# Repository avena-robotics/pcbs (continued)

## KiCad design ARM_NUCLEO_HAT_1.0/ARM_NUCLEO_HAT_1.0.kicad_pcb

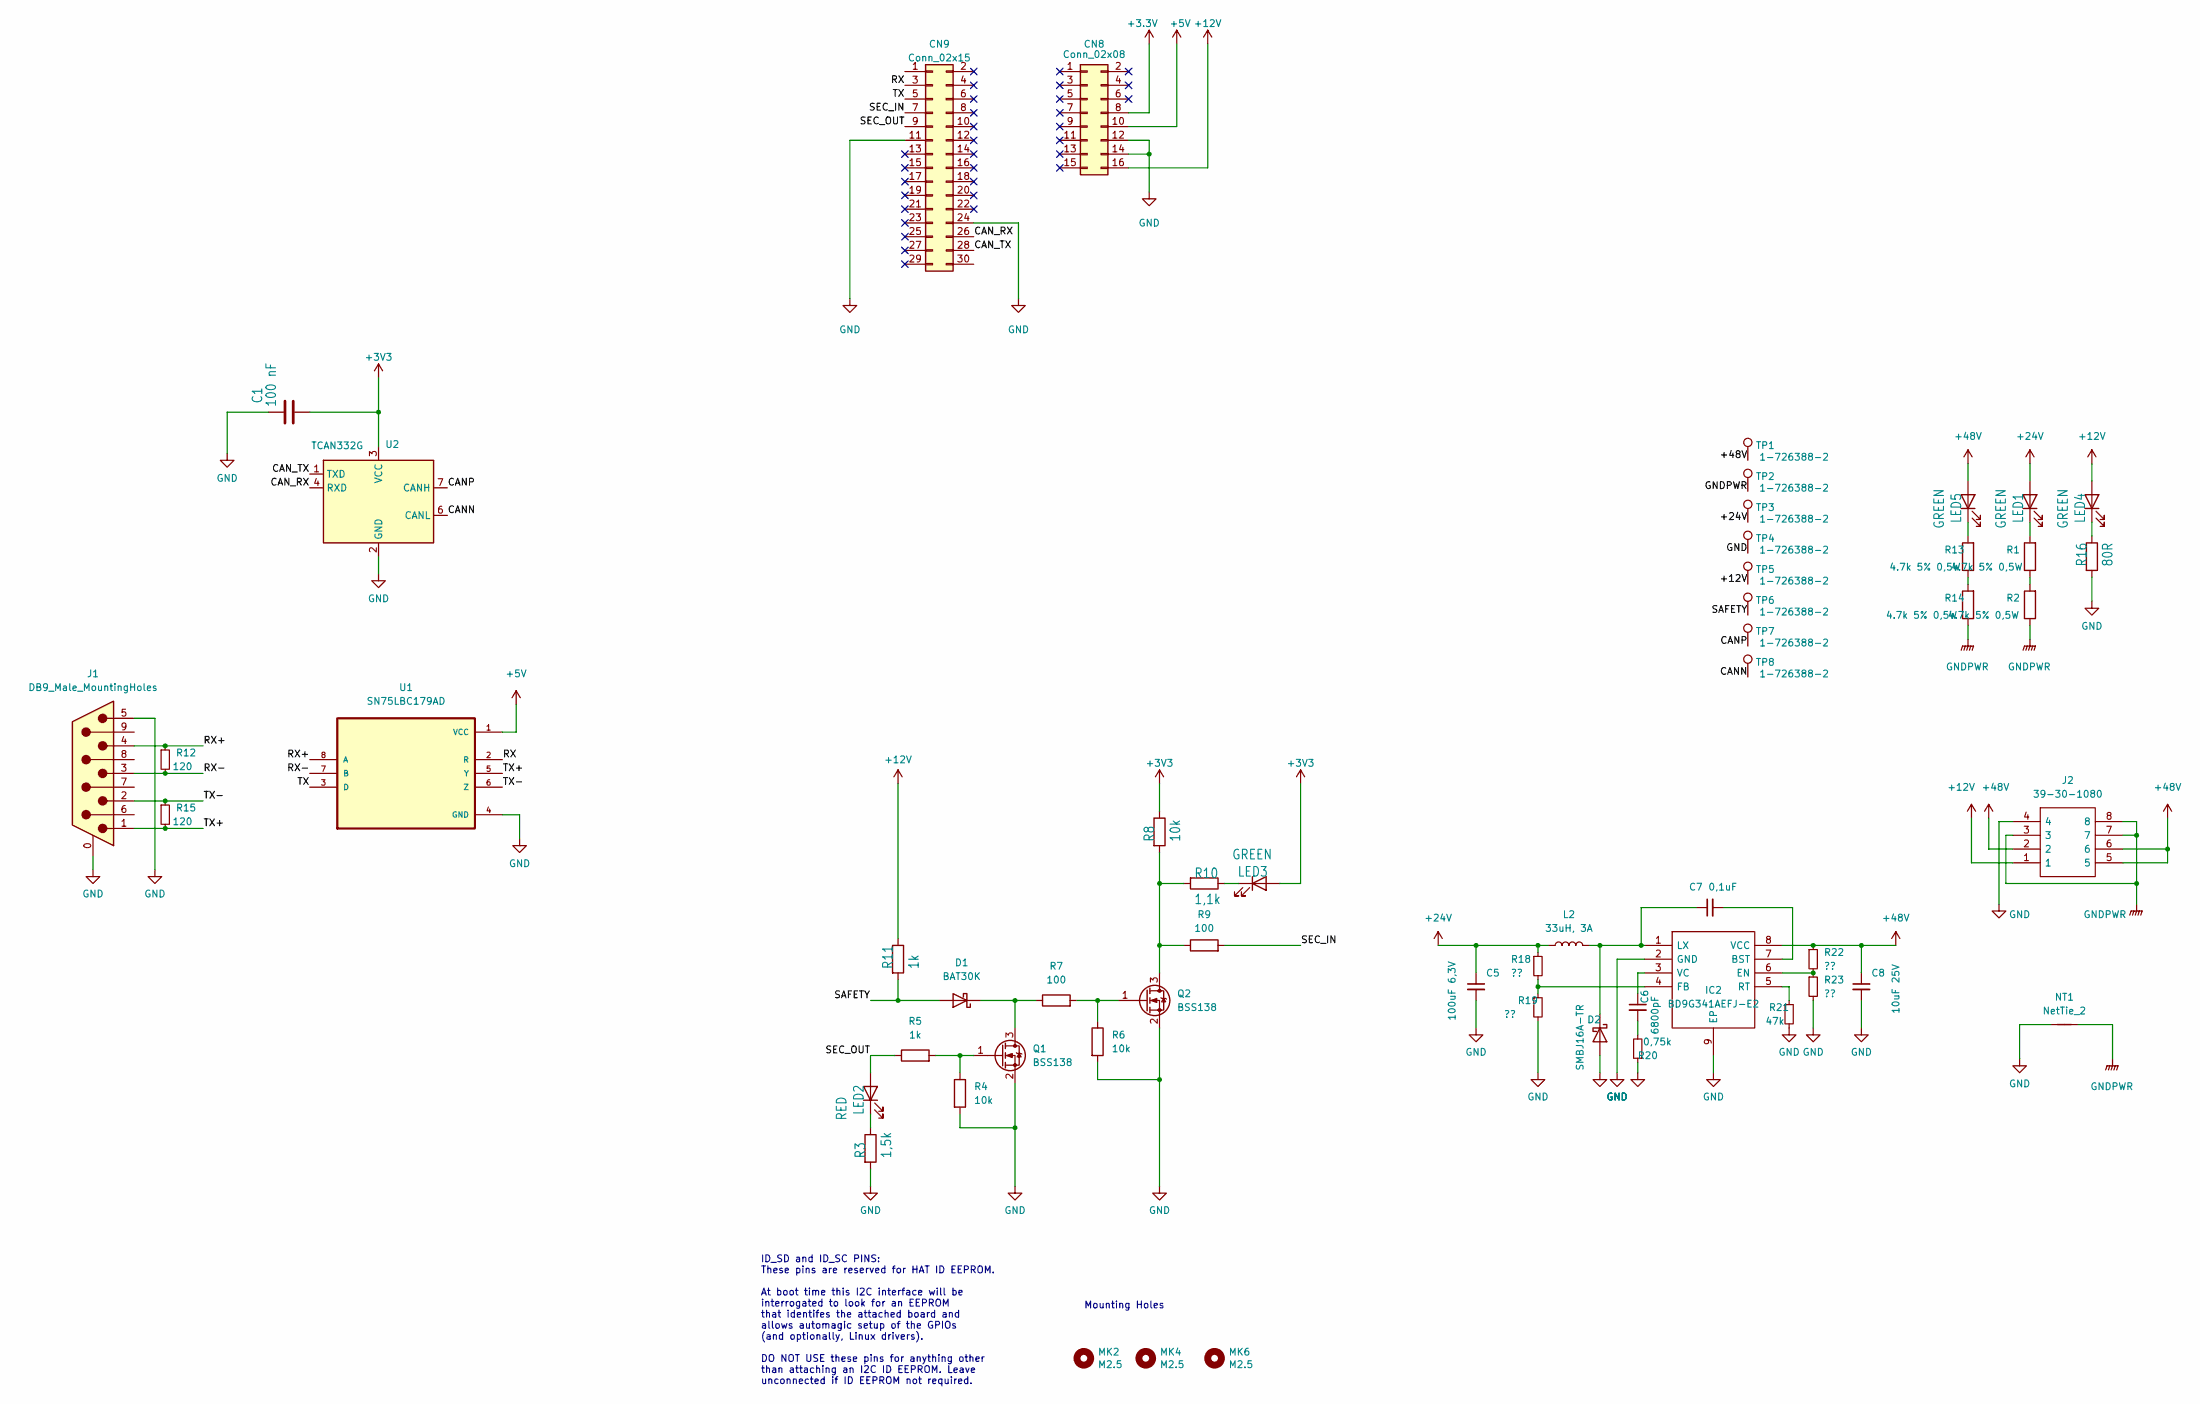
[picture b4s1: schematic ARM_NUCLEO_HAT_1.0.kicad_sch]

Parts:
C1: 100 nF; C_0603_1608Metric_Pad1.08x0.95mm_HandSolder
C5: 100uF 6,3V; C_1206_3216Metric_Pad1.33x1.80mm_HandSolder
C6: 6800pF; C_0603_1608Metric_Pad1.08x0.95mm_HandSolder
C7: 0,1uF; C_0603_1608Metric_Pad1.08x0.95mm_HandSolder
C8: 10uF 25V; C_0603_1608Metric_Pad1.08x0.95mm_HandSolder
CN8: Conn_02x08; PinSocket_2x08_P2.54mm_Vertical
CN9: Conn_02x15; PinSocket_2x15_P2.54mm_Vertical
D1: BAT30K; D_0603_1608Metric_Pad1.05x0.95mm_HandSolder
D2: SMBJ16A-TR; D_SMB_Handsoldering
IC2: BD9G341AEFJ-E2; SOIC127P600X100-9N; Mouser Part Number 755-BD9G341AEFJ-E2
J1: DB9_Male_MountingHoles; DSUB-9_Male_Horizontal_P2.77x2.84mm_EdgePinOffset7.70mm_Hou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
J2: 39-30-1080; 39301080; Mouser Part Number 538-39-30-1080
L2: 33uH, 3A; MPEV1D1040L330
LED1, LED3, LED4, LED5: GREEN; D_0603_1608Metric_Pad1.05x0.95mm_HandSolder
LED2: RED; D_0603_1608Metric_Pad1.05x0.95mm_HandSolder
MK2, MK4, MK6: M2.5; MountingHole_2.7mm_M2.5
NT1: NetTie_2; NetTie-2_SMD_Pad0.5mm
Q1, Q2: BSS138; SOT-23
R1, R2, R13, R14: 4.7k 5% 0,5W; R_0805_2012Metric_Pad1.20x1.40mm_HandSolder
R3: 1,5k; R_0603_1608Metric_Pad0.98x0.95mm_HandSolder
R4, R6, R8: 10k; R_0603_1608Metric_Pad0.98x0.95mm_HandSolder
R5, R11: 1k; R_0603_1608Metric_Pad0.98x0.95mm_HandSolder
R7, R9: 100; R_0603_1608Metric_Pad0.98x0.95mm_HandSolder
R10: 1,1k; R_0603_1608Metric_Pad0.98x0.95mm_HandSolder
R12, R15: 120; R_0603_1608Metric_Pad0.98x0.95mm_HandSolder
R16: 80R; R_0603_1608Metric_Pad0.98x0.95mm_HandSolder
R18, R19, R22, R23: ??; R_0603_1608Metric_Pad0.98x0.95mm_HandSolder
R20: 0,75k; R_0603_1608Metric_Pad0.98x0.95mm_HandSolder
R21: 47k; R_0603_1608Metric_Pad0.98x0.95mm_HandSolder
TP1, TP2, TP3, TP4, TP5, TP6, TP7, TP8: 1-726388-2; 61-1537-11-0031
U1: SN75LBC179AD; SOIC127P599X175-8N
U2: TCAN332G; SO-8_3.9x4.9mm_P1.27mm

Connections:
+5V: CN8.10, U1.1 (VCC)
+12V: CN8.16, J2.1, LED4.2 (A), R11.1, TP5.1
+24V: C5.1, L2.1, LED1.2 (A), R18.1, TP3.1
+48V: C8.1, IC2.8 (VCC), J2.2, J2.5, J2.6, LED5.2 (A), R22.1, TP1.1
/CANN: TP8.1, U2.6 (CANL)
/CANP: TP7.1, U2.7 (CANH)
/CAN_RX: CN9.26, U2.4 (RXD)
/CAN_TX: CN9.28, U2.1 (TXD)
/RX: CN9.3, U1.2 (R)
/RX+: J1.4, R12.1, U1.8 (A)
/RX-: J1.3, R12.2, U1.7 (B)
/SAFETY: D1.2 (A), R11.2, TP6.1
/SEC_IN: CN9.7, R9.2
/SEC_OUT: CN9.9, LED2.2 (A), R5.1
/TX: CN9.5, U1.3 (D)
/TX+: J1.1, R15.2, U1.5 (Y)
/TX-: J1.2, R15.1, U1.6 (Z)
GND: C1.2, C5.2, C8.2, CN8.12, CN8.14, CN9.11, CN9.24, D2.2 (A), IC2.2 (GND), IC2.9 (EP), J1.0 (PAD), J1.5, J2.4, NT1.1, Q1.2 (S), Q2.2 (S), R3.2, R4.2, R6.2, R16.2, R19.2, R20.1, R21.2, R23.2, TP4.1, U1.4 (GND), U2.2 (GND)
GNDPWR: J2.3, J2.7, J2.8, NT1.2, R2.1, R14.1, TP2.1
unnamed: C6.1, IC2.3 (VC)
unnamed: C6.2, R20.2
unnamed: C7.1, D2.1 (K), IC2.1 (LX), L2.2
unnamed: C7.2, IC2.7 (BST)
unnamed: D1.1 (K), Q1.3 (D), R7.1
unnamed: IC2.4 (FB), R18.2, R19.1
unnamed: IC2.5 (RT), R21.1
unnamed: IC2.6 (EN), R22.2, R23.1
unnamed: LED1.1 (K), R1.2
unnamed: LED2.1 (K), R3.1
unnamed: LED3.1 (K), R10.1
unnamed: LED4.1 (K), R16.1
unnamed: LED5.1 (K), R13.2
unnamed: Q1.1 (G), R4.1, R5.2
unnamed: Q2.1 (G), R6.1, R7.2
unnamed: Q2.3 (D), R8.2, R9.1, R10.2
unnamed: R1.1, R2.2
unnamed: R13.1, R14.2

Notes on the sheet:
ID_SD and ID_SC PINS: These pins are reserved for HAT ID EEPROM. At boot time this I2C interface will be interrogated to look for an EEPROM that identifes the attached board and allows automagic setup of the GPIOs (and optionally, Linux drivers). DO NOT USE these pins for anything other than attach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
Mounting Holes

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
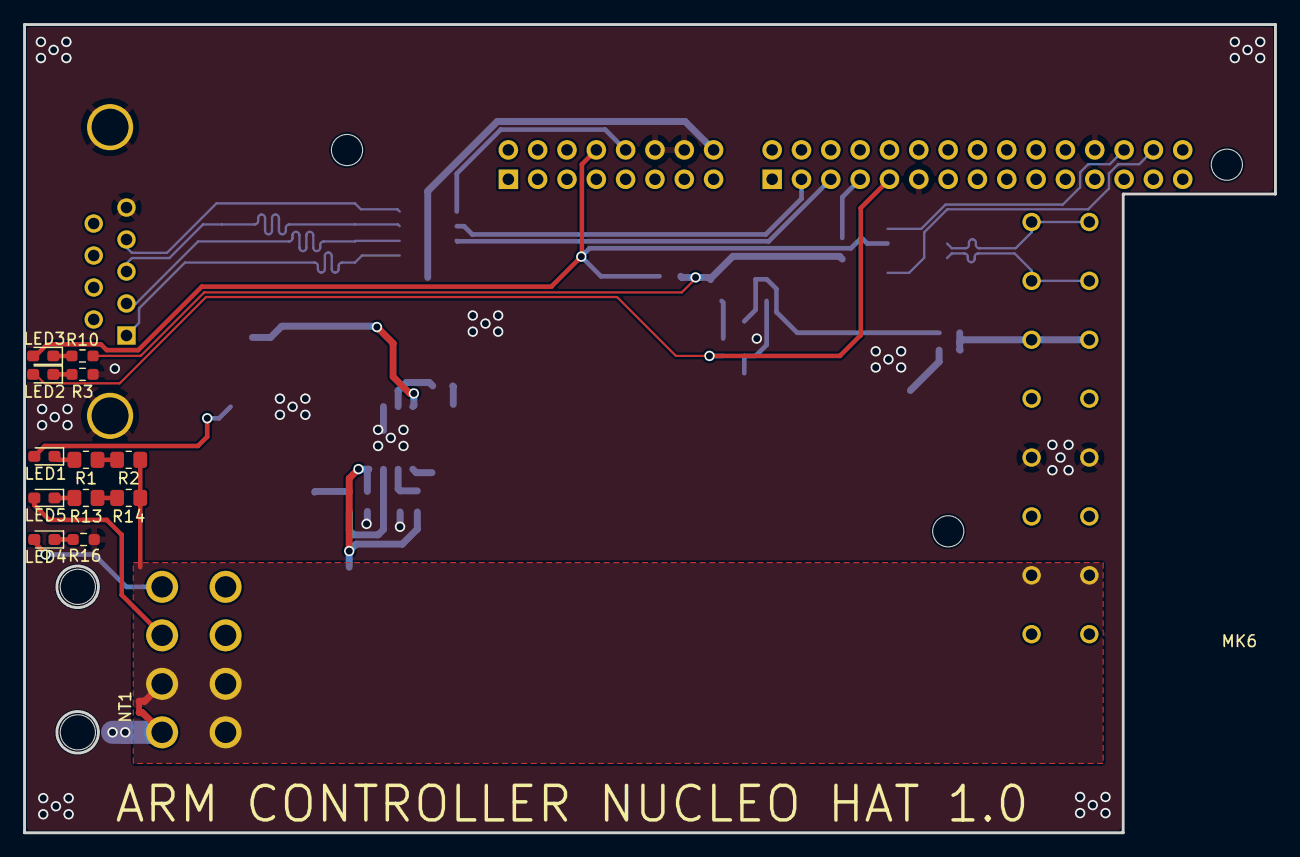
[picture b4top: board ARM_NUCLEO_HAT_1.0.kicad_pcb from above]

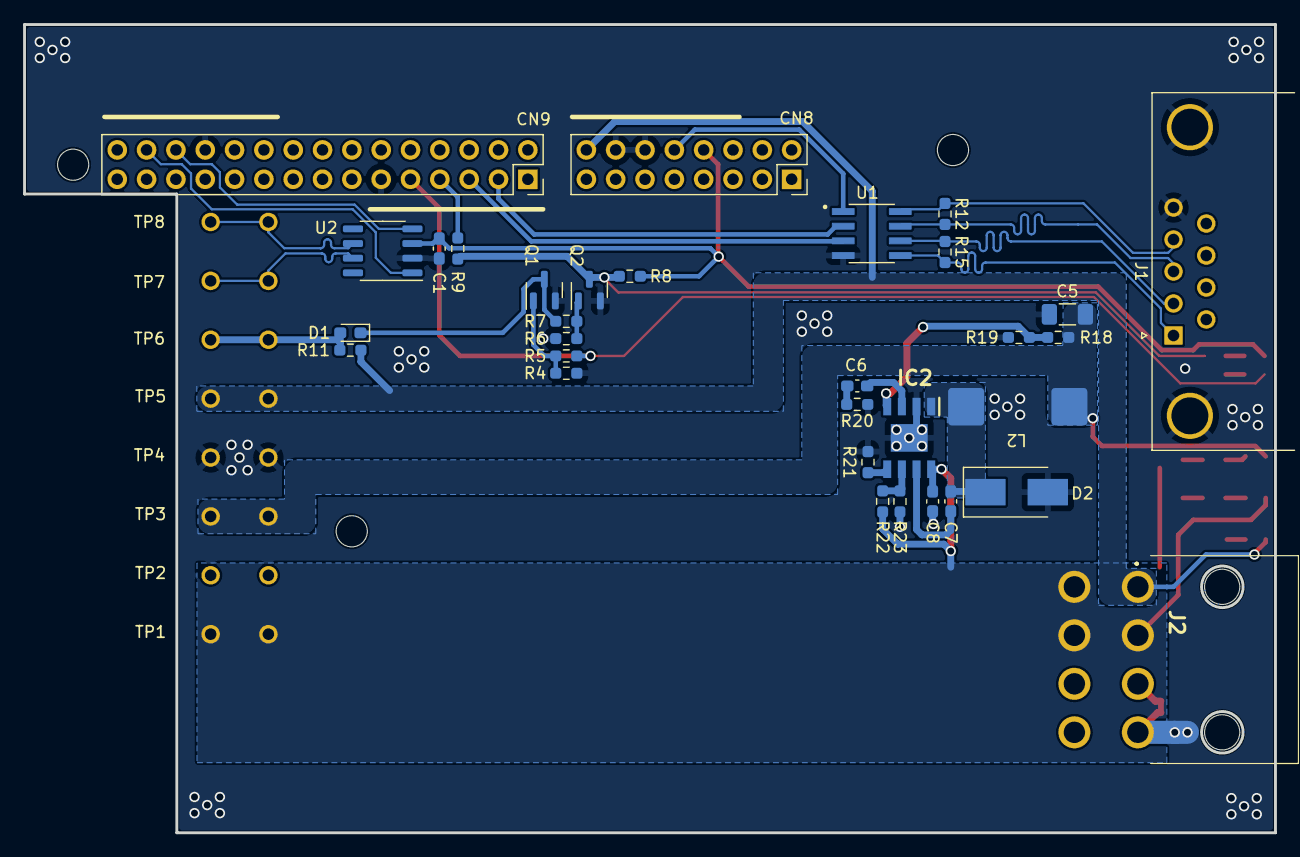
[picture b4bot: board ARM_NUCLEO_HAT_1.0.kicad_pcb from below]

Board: 2 copper layers, 108.3 x 70.0 mm, 56 parts (40 on the bottom side), 38 nets.

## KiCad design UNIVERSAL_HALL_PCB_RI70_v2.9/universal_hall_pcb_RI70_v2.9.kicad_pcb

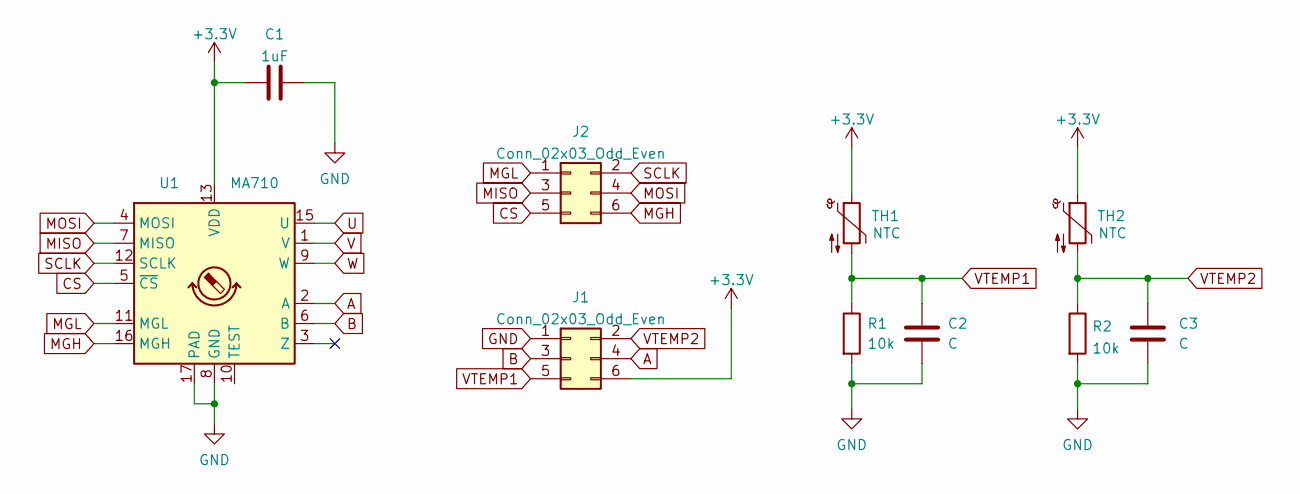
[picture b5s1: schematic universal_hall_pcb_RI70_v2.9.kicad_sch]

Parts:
C1: 1uF; C_0603_1608Metric_Pad1.08x0.95mm_HandSolder
C2, C3: C; C_0603_1608Metric_Pad1.08x0.95mm_HandSolder
J1, J2: Conn_02x03_Odd_Even; PinSocket_2x03_P2.54mm_Vertical
R1, R2: 10k; R_0603_1608Metric_Pad0.98x0.95mm_HandSolder
TH1, TH2: NTC; PinHeader_1x02_P2.54mm_Vertical
U1: MA710; VQFN-16-1EP_3x3mm_P0.5mm_EP1.8x1.8mm

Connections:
+3V3: C1.1, J1.6, TH1.1, TH2.1, U1.13 (VDD)
A: J1.4, U1.2 (A)
B: J1.3, U1.6 (B)
CS: J2.5, U1.5 (~CS)
GND: C1.2, C2.2, C3.2, J1.1, R1.2, R2.2, U1.8 (GND), U1.17 (PAD)
MGH: J2.6, U1.16 (MGH)
MGL: J2.1, U1.11 (MGL)
MISO: J2.3, U1.7 (MISO)
MOSI: J2.4, U1.4 (MOSI)
SCLK: J2.2, U1.12 (SCLK)
U: U1.15 (U)
V: U1.1 (V)
VTEMP1: C2.1, J1.5, R1.1, TH1.2
VTEMP2: C3.1, J1.2, R2.1, TH2.2
W: U1.9 (W)

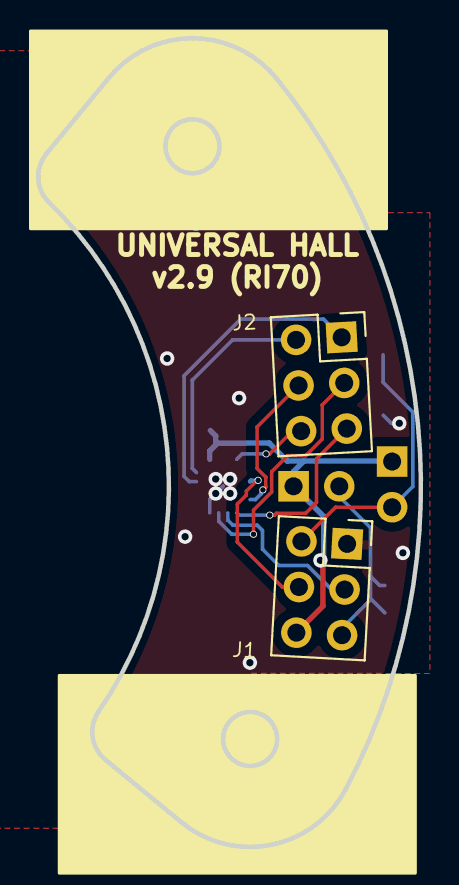
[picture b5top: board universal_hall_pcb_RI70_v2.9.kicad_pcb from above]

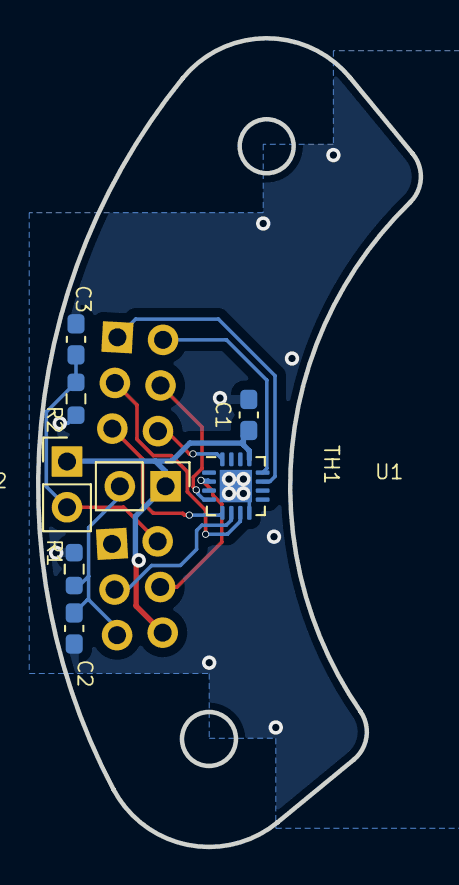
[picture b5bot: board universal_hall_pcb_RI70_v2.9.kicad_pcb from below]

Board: 2 copper layers, 21.3 x 44.9 mm, 10 parts (8 on the bottom side), 12 nets.

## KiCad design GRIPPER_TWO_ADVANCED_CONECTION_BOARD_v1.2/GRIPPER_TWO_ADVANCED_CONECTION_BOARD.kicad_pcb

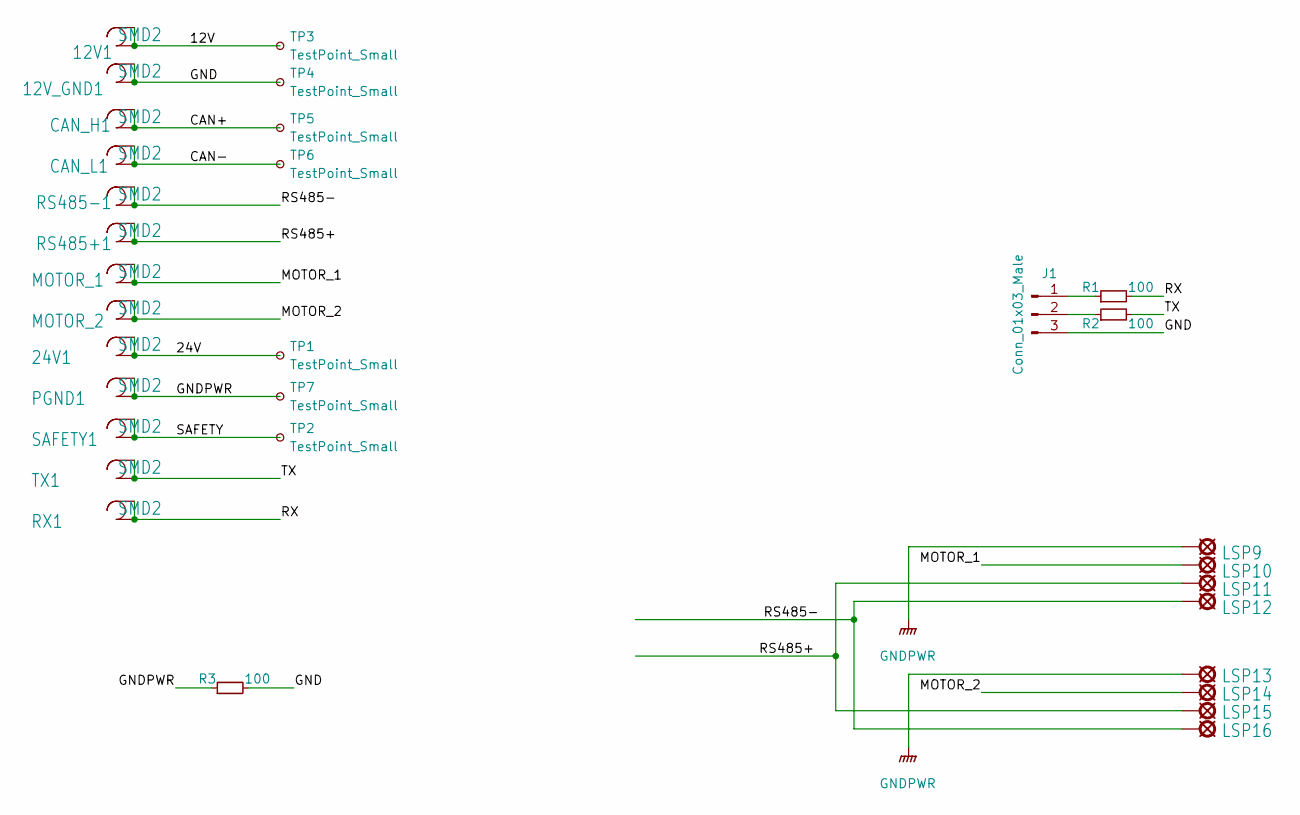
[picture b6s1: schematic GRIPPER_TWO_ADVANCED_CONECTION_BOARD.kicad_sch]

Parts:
12V1, 12V_GND1, 24V1: SMD2; SMD1,27-2,54
CAN_H1: SMD2; SMD1,27-2,54
CAN_L1: SMD2; SMD1,27-2,54
J1: Conn_01x03_Male; PinHeader_1x03_P2.54mm_Vertical
LSP9, LSP10, LSP11, LSP12, LSP13, LSP14, LSP15, LSP16: SE11
MOTOR_1, MOTOR_2: SMD2; SMD1,27-2,54
PGND1: SMD2; SMD1,27-2,54
R1, R2, R3: 100; R_0603_1608Metric_Pad0.98x0.95mm_HandSolder
RS485+1, RS485-1: SMD2; SMD1,27-2,54
RX1: SMD2; SMD1,27-2,54
SAFETY1: SMD2; SMD1,27-2,54
TP1, TP2, TP3, TP4, TP5, TP6, TP7: TestPoint_Small; TestPoint_Pad_1.0x1.0mm
TX1: SMD2; SMD1,27-2,54

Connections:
/12V: 12V1.1, 12V1.2, TP3.1
/24V: 24V1.1, 24V1.2, TP1.1
/CAN+: CAN_H1.1, CAN_H1.2, TP5.1
/CAN-: CAN_L1.1, CAN_L1.2, TP6.1
/GND: 12V_GND1.1, 12V_GND1.2, J1.3, R3.2, TP4.1
/MOTOR_1: LSP10.MP, MOTOR_1.1, MOTOR_1.2
/MOTOR_2: LSP14.MP, MOTOR_2.1, MOTOR_2.2
/RS485+: LSP11.MP, LSP15.MP, RS485+1.1, RS485+1.2
/RS485-: LSP12.MP, LSP16.MP, RS485-1.1, RS485-1.2
/RX: R1.2, RX1.1, RX1.2
/SAFETY: SAFETY1.1, SAFETY1.2, TP2.1
/TX: R2.2, TX1.1, TX1.2
GNDPWR: LSP9.MP, LSP13.MP, PGND1.1, PGND1.2, R3.1, TP7.1
unnamed: J1.1, R1.1
unnamed: J1.2, R2.1

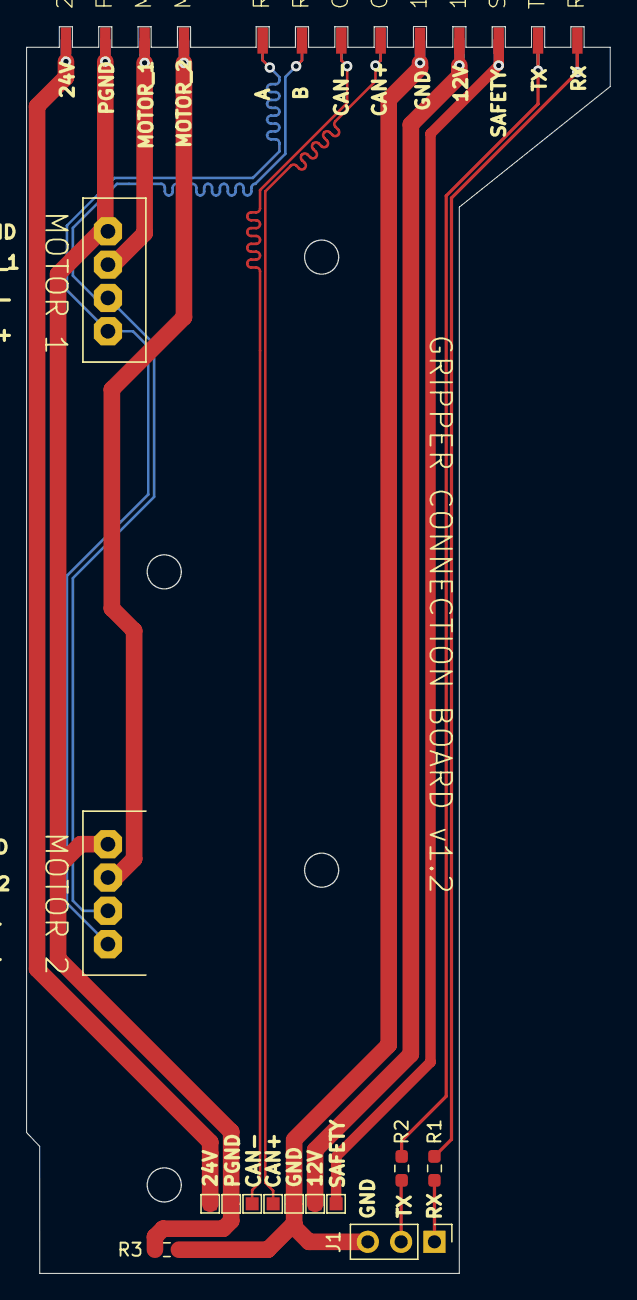
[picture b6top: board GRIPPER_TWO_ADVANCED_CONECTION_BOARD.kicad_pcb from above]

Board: 2 copper layers, 44.5 x 95.1 mm, 32 parts (0 on the bottom side), 15 nets.
